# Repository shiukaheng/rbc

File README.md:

# 🤖 RoboCapture
A photogrammetry robot designed from scratch to autonomously scan indoor spaces.

## 🛠 Development

- **Cross-Platform**: This repository is designed to be cross-platform, working on Windows, MacOS, and Linux. We leverage Docker and the devcontainer extension in VSCode to achieve this.
  
- **Testing**: Most of the development and testing have been done on Linux. However, it might require slight adjustments when setting up on other operating systems.

### 🔧 Pre-requisites

1. `$(hostname).local` should be broadcasted on the network using mDNS. This applies to both the robot and the development computer.
2. Docker must be running on a Linux environment.

### 🍎 MacOS Specifics

If you're on a Mac, you might need to adjust the Docker permissions:
```bash
sudo chown -R $(whoami) ~/.docker
```
This ensures Docker can run without requiring sudo every time.

### 🖥️ X11 Authentication

For enabling X11 forwarding, execute the following command on the host computer:
```bash
xhost +local:docker
```

### 📝 Notes
Please double-check the file permissions before making a commit to ensure they are appropriate, due to docker created files being owned by `root`. Fix shall be issued soon.

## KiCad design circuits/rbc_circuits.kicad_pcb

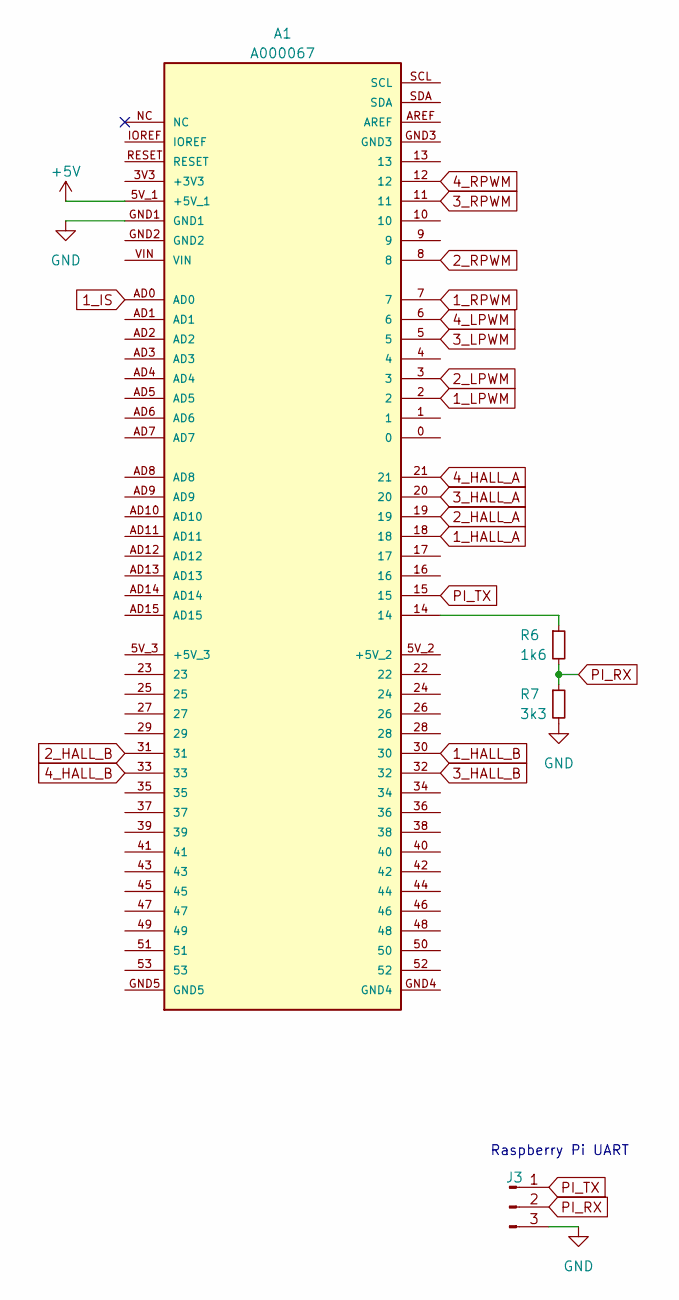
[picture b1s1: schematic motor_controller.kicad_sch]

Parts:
A1: A000067; ARDUINO_A000067
J3: Conn_01x03_Pin
R6: 1k6
R7: 3k3

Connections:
1_HALL_A: A1.18; also elsewhere on the board
1_HALL_B: A1.30; also elsewhere on the board
1_LPWM: A1.2; also elsewhere on the board
1_RPWM: A1.7; also elsewhere on the board
2_HALL_A: A1.19; also elsewhere on the board
2_HALL_B: A1.31; also elsewhere on the board
2_IS: A1.AD1; also elsewhere on the board
2_LPWM: A1.3; also elsewhere on the board
2_RPWM: A1.8; also elsewhere on the board
3_HALL_A: A1.20; also elsewhere on the board
3_HALL_B: A1.32; also elsewhere on the board
3_IS: A1.AD2; also elsewhere on the board
3_LPWM: A1.5; also elsewhere on the board
3_RPWM: A1.11; also elsewhere on the board
4_HALL_A: A1.21; also elsewhere on the board
4_HALL_B: A1.33; also elsewhere on the board
4_IS: A1.AD3; also elsewhere on the board
4_LPWM: A1.6; also elsewhere on the board
4_RPWM: A1.12; also elsewhere on the board
+5V: A1.5V_1 (+5V_1); also elsewhere on the board
PI_TX: A1.15, J3.1

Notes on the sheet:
Raspberry Pi UART

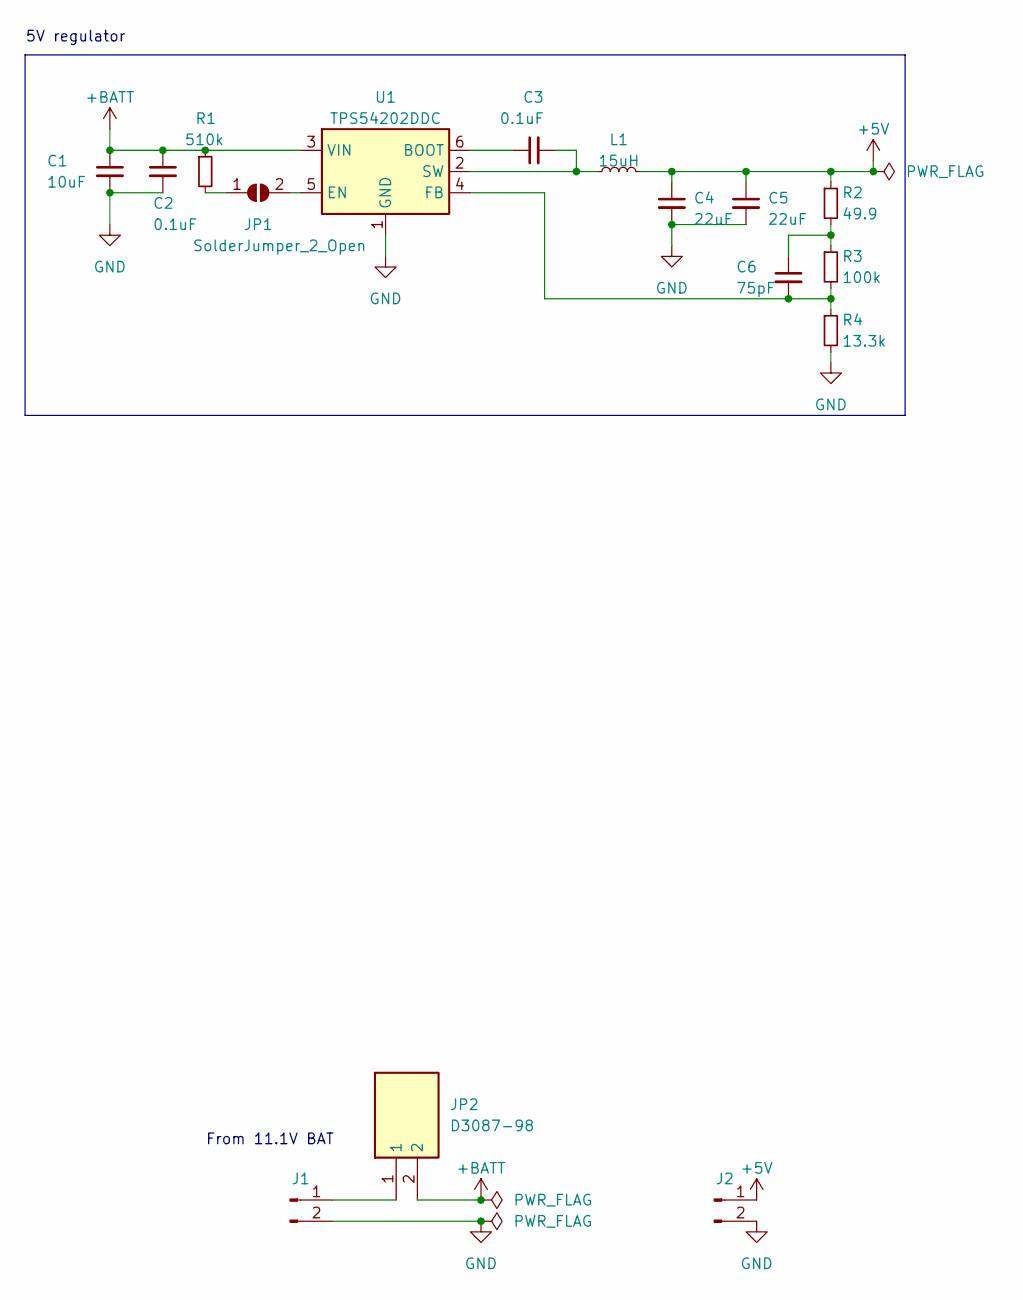
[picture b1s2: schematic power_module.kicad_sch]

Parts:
C1: 10uF; C_1206_3216Metric_Pad1.33x1.80mm_HandSolder
C2, C3: 0.1uF; C_0603_1608Metric_Pad1.08x0.95mm_HandSolder
C4, C5: 22uF; C_1206_3216Metric_Pad1.33x1.80mm_HandSolder
C6: 75pF; C_0805_2012Metric_Pad1.18x1.45mm_HandSolder
J1: Conn_01x02_Pin; TerminalBlock_Phoenix_MKDS-3-2-5.08_1x02_P5.08mm_Horizontal
J2: Conn_01x02_Pin; PinHeader_1x02_P2.54mm_Vertical
JP1: SolderJumper_2_Open; SolderJumper-2_P1.3mm_Open_RoundedPad1.0x1.5mm
JP2: D3087-98; D308798; Mouser Part Number 855-D3087-98
L1: 15uH; IND_LQH3NPH150MMEL
R1: 510k; R_0805_2012Metric_Pad1.20x1.40mm_HandSolder
R2: 49.9; R_0805_2012Metric_Pad1.20x1.40mm_HandSolder
R3: 100k; R_1206_3216Metric_Pad1.30x1.75mm_HandSolder
R4: 13.3k; R_0805_2012Metric_Pad1.20x1.40mm_HandSolder
U1: TPS54202DDC; SOT-23-6

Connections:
+5V: C4.1, C5.1, J2.1, L1.2, R2.1; also elsewhere on the board
+BATT: C1.1, C2.1, JP2.2, R1.1, U1.3 (VIN)
unnamed: C6.1, R2.2, R3.1
unnamed: J1.1, JP2.1
unnamed: JP1.1 (A), R1.2
unnamed: JP1.2 (B), U1.5 (EN)
unnamed: C3.1, U1.6 (BOOT)
unnamed: C6.2, R3.2, R4.1, U1.4 (FB)
unnamed: C3.2, L1.1, U1.2 (SW)

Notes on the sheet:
From 11.1V BAT
5V regulator

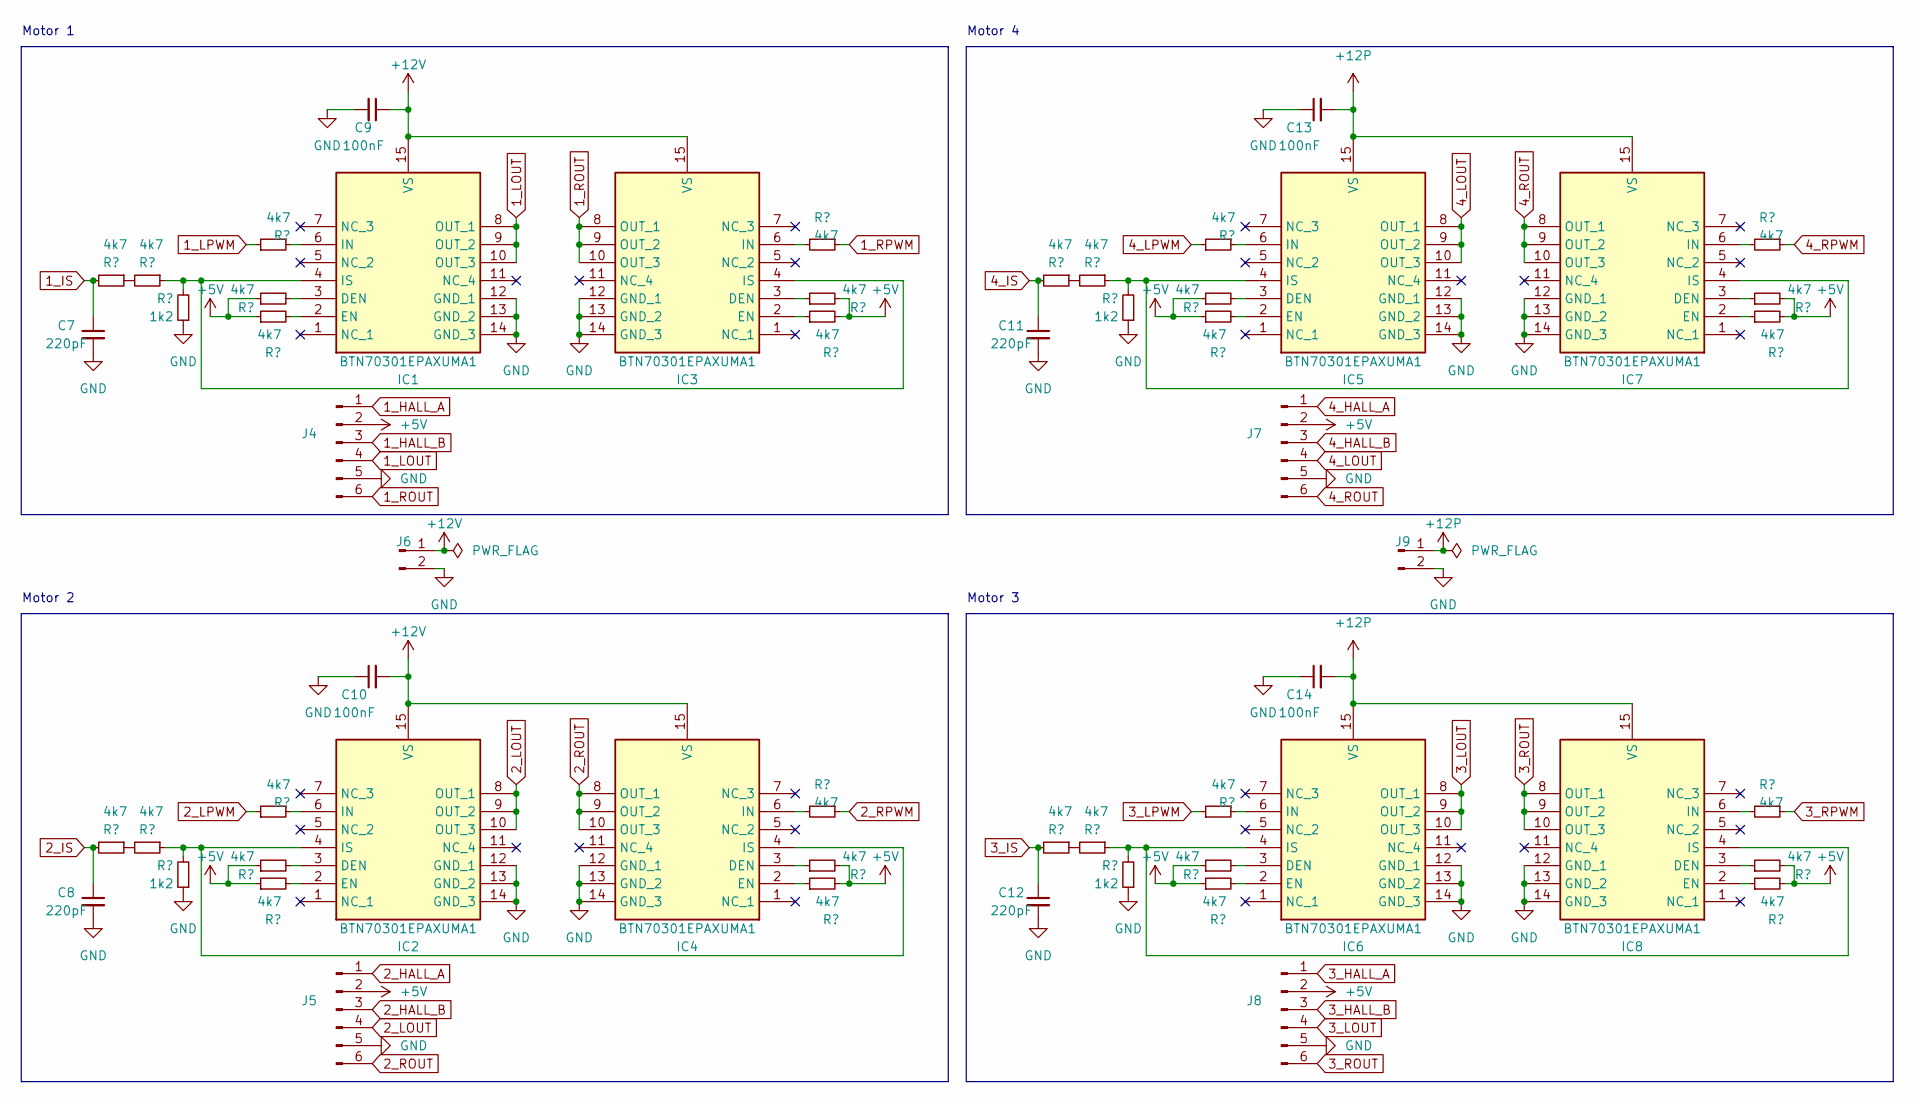
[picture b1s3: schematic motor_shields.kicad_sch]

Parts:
C7, C8, C11, C12: 220pF; C_0402_1005Metric_Pad0.74x0.62mm_HandSolder
C9, C10, C13, C14: 100nF; C_0603_1608Metric_Pad1.08x0.95mm_HandSolder
IC1, IC2, IC3, IC4, IC5, IC6, IC7, IC8: BTN70301EPAXUMA1; Infineon_PG-TSDSO-14-22_custom; Mouser Part Number 726-BTN70301EPAXUMA1
J4, J5, J7, J8: Conn_01x06_Pin; Molex_Micro-Fit_3.0_43045-0612_2x03_P3.00mm_Vertical
J6, J9: Conn_01x02_Pin; TerminalBlock_Phoenix_MKDS-3-2-5.08_1x02_P5.08mm_Horizontal
R7, R8, R9, R10, R13, R14, R15, R16, R17, R18, R19, R20, R21, R22, R23, R24, R25, R26, R27, R28, R31, R32, R33, R34, R35, R36, R37, R38, R39, R40, R41, R42: 4k7; R_1206_3216Metric_Pad1.30x1.75mm_HandSolder
R11, R12, R29, R30: 1k2; R_1206_3216Metric_Pad1.30x1.75mm_HandSolder

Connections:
1_HALL_A: J4.1; also elsewhere on the board
1_HALL_B: J4.3; also elsewhere on the board
1_LOUT: IC1.8 (OUT_1), IC1.9 (OUT_2), IC1.10 (OUT_3), J4.4
1_LPWM: R13.1; also elsewhere on the board
1_ROUT: IC3.8 (OUT_1), IC3.9 (OUT_2), IC3.10 (OUT_3), J4.6
1_RPWM: R19.1; also elsewhere on the board
2_HALL_A: J5.1; also elsewhere on the board
2_HALL_B: J5.3; also elsewhere on the board
2_IS: C8.1, R8.2; also elsewhere on the board
2_LOUT: IC2.8 (OUT_1), IC2.9 (OUT_2), IC2.10 (OUT_3), J5.4
2_LPWM: R16.1; also elsewhere on the board
2_ROUT: IC4.8 (OUT_1), IC4.9 (OUT_2), IC4.10 (OUT_3), J5.6
2_RPWM: R22.1; also elsewhere on the board
3_HALL_A: J8.1; also elsewhere on the board
3_HALL_B: J8.3; also elsewhere on the board
3_IS: C12.1, R26.2; also elsewhere on the board
3_LOUT: IC6.8 (OUT_1), IC6.9 (OUT_2), IC6.10 (OUT_3), J8.4
3_LPWM: R34.1; also elsewhere on the board
3_ROUT: IC8.8 (OUT_1), IC8.9 (OUT_2), IC8.10 (OUT_3), J8.6
3_RPWM: R40.1; also elsewhere on the board
4_HALL_A: J7.1; also elsewhere on the board
4_HALL_B: J7.3; also elsewhere on the board
4_IS: C11.1, R25.2; also elsewhere on the board
4_LOUT: IC5.8 (OUT_1), IC5.9 (OUT_2), IC5.10 (OUT_3), J7.4
4_LPWM: R31.1; also elsewhere on the board
4_ROUT: IC7.8 (OUT_1), IC7.9 (OUT_2), IC7.10 (OUT_3), J7.6
4_RPWM: R37.1; also elsewhere on the board
+5V: J4.2, J5.2, J7.2, J8.2, R14.1, R15.1, R17.1, R18.1, R20.2, R21.2, R23.2, R24.2, R32.1, R33.1, R35.1, R36.1, R38.2, R39.2, R41.2, R42.2; also elsewhere on the board
+12P: C13.2, C14.2, IC5.15 (VS), IC6.15 (VS), IC7.15 (VS), IC8.15 (VS), J9.1
+12V: C9.1, C10.2, IC1.15 (VS), IC2.15 (VS), IC3.15 (VS), IC4.15 (VS), J6.1
unnamed: IC1.3 (DEN), R14.2
unnamed: IC1.2 (EN), R15.2
unnamed: IC1.6 (IN), R13.2
unnamed: IC1.4 (IS), IC3.4 (IS), R9.1, R11.2
unnamed: IC2.3 (DEN), R17.2
unnamed: IC2.2 (EN), R18.2
unnamed: IC2.6 (IN), R16.2
unnamed: IC2.4 (IS), IC4.4 (IS), R10.1, R12.2
unnamed: IC3.3 (DEN), R20.1
unnamed: IC3.2 (EN), R21.1
unnamed: IC3.6 (IN), R19.2
unnamed: IC4.3 (DEN), R23.1
unnamed: IC4.2 (EN), R24.1
unnamed: IC4.6 (IN), R22.2
unnamed: IC5.3 (DEN), R32.2
unnamed: IC5.2 (EN), R33.2
unnamed: IC5.6 (IN), R31.2
unnamed: IC5.4 (IS), IC7.4 (IS), R27.1, R29.2
unnamed: IC6.3 (DEN), R35.2
unnamed: IC6.2 (EN), R36.2
unnamed: IC6.6 (IN), R34.2
unnamed: IC6.4 (IS), IC8.4 (IS), R28.1, R30.2
unnamed: IC7.3 (DEN), R38.1
unnamed: IC7.2 (EN), R39.1
unnamed: IC7.6 (IN), R37.2
unnamed: IC8.3 (DEN), R41.1
unnamed: IC8.2 (EN), R42.1
unnamed: IC8.6 (IN), R40.2
unnamed: R8.1, R10.2
unnamed: R25.1, R27.2
unnamed: R26.1, R28.2

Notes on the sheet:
Motor 2
Motor 3
Motor 4
Motor 1

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
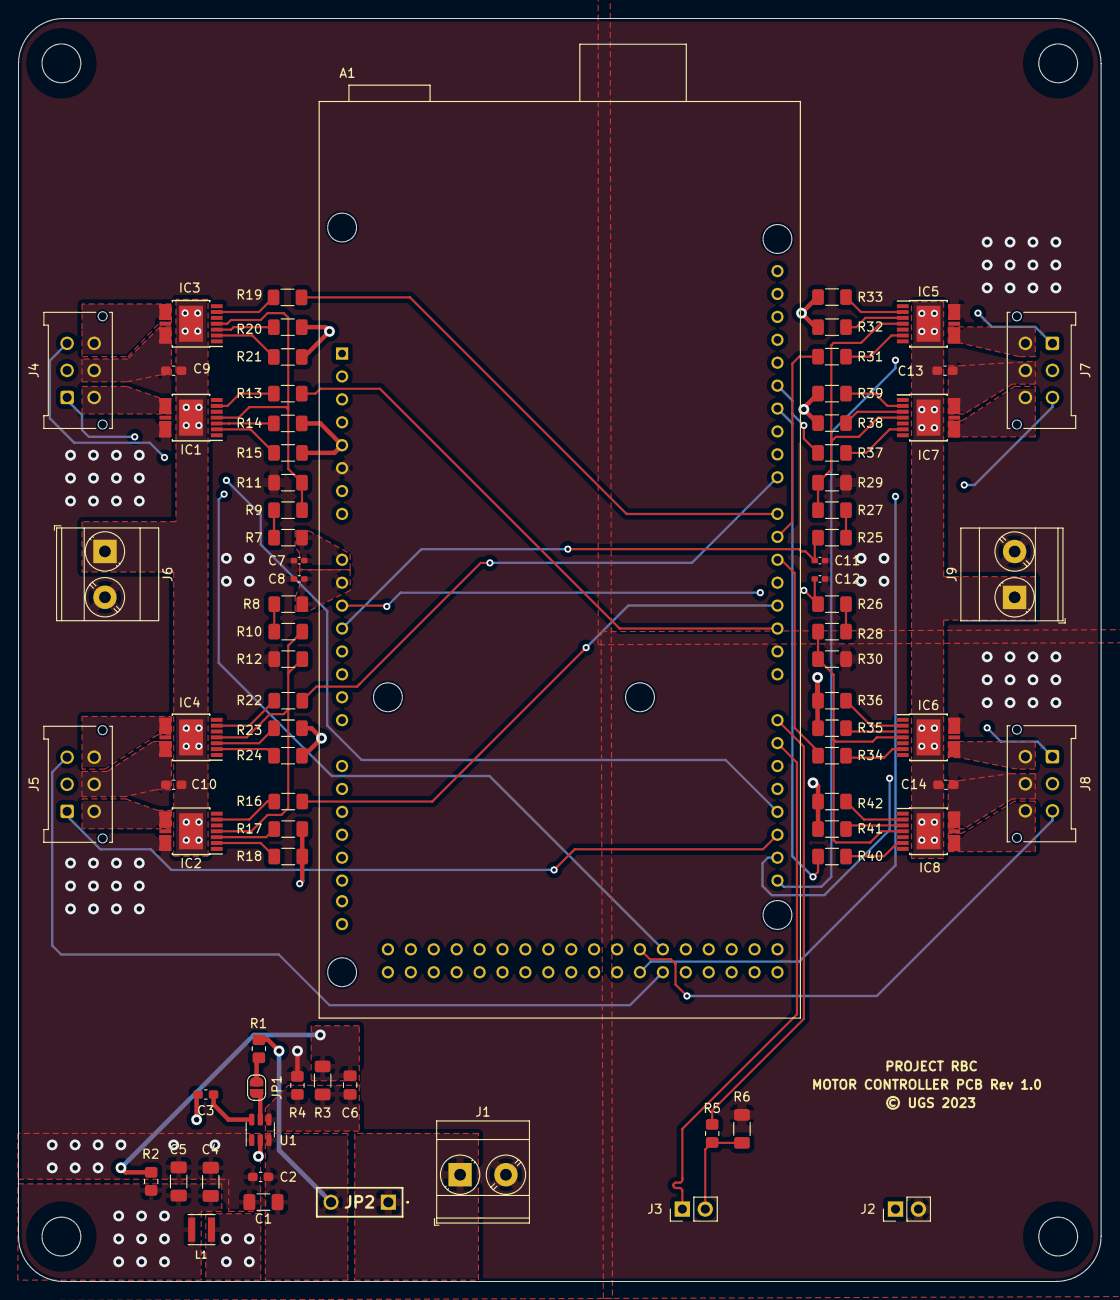
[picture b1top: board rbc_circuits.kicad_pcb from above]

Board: 4 copper layers, 120.0 x 140.0 mm, 78 parts (0 on the bottom side), 75 nets.

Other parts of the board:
R5: 1k6; R_0805_2012Metric_Pad1.20x1.40mm_HandSolder

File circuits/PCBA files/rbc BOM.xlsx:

Comment | Designator | Footprint | JLCPCB Part #
DNP | A1 | A000067:ARDUINO_A000067
10uF | C1 | Capacitor_SMD:C_1206_3216Metric_Pad1.33x1.80mm_HandSolder | C396795
0.1uF | C2, C3 | Capacitor_SMD:C_0603_1608Metric_Pad1.08x0.95mm_HandSolder
22uF | C4, C5 | Capacitor_SMD:C_1206_3216Metric_Pad1.33x1.80mm_HandSolder | C909845
75pF | C6 | Capacitor_SMD:C_0805_2012Metric_Pad1.18x1.45mm_HandSolder
220pF | C7, C8, C11, C12 | Capacitor_SMD:C_0402_1005Metric_Pad0.74x0.62mm_HandSolder | C513697
100nF | C9, C10, C13, C14 | Capacitor_SMD:C_0603_1608Metric_Pad1.08x0.95mm_HandSolder | C307348
BTN70301EPAXUMA1 | IC1, IC2, IC3, IC4, IC5, IC6, IC7, IC8 | Infineon_PG-TSDSO-14-22 | C3655686
Conn_01x02_Pin | J1, J6, J9 | TerminalBlock_Phoenix:TerminalBlock_Phoenix_MKDS-3-2-5.08_1x02_P5.08mm_Horizont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 | C89120
DNP | J2, J3 | Connector_PinHeader_2.54mm:PinHeader_1x02_P2.54mm_Vertical
Conn_01x06_Pin | J4, J5, J7, J8 | Connector_Molex:Molex_Micro-Fit_3.0_43045-0612_2x03_P3.00mm_Vertical | C234188
DNP | JP1 | Jumper:SolderJumper-2_P1.3mm_Open_RoundedPad1.0x1.5mm
DNP | JP2 | D308798
15uH | L1 | LQH3NPH150MMEL:IND_LQH3NPH150MMEL | C668450
510k | R1 | Resistor_SMD:R_0805_2012Metric_Pad1.20x1.40mm_HandSolder | C316820
49.9 | R2 | Resistor_SMD:R_0805_2012Metric_Pad1.20x1.40mm_HandSolder | C164002
100k | R3 | Resistor_SMD:R_1206_3216Metric_Pad1.30x1.75mm_HandSolder | C881326
13.3k | R4 | Resistor_SMD:R_0805_2012Metric_Pad1.20x1.40mm_HandSolder | C170785
1.6k | R5 | Resistor_SMD:R_0805_2012Metric_Pad1.20x1.40mm_HandSolder | C316776
3.3k | R6 | Resistor_SMD:R_1206_3216Metric_Pad1.30x1.75mm_HandSolder | C104771
4.7k | R7, R8, R9, R10, R13, R14, R15, R16, R17, R18, R19, R20, R21, R22, R23, R24, R2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 | Resistor_SMD:R_1206_3216Metric_Pad1.30x1.75mm_HandSolder | C432834
1.2k | R11, R12, R29, R30 | Resistor_SMD:R_1206_3216Metric_Pad1.30x1.75mm_HandSolder | C340507
TPS54202DDC | U1 | Package_TO_SOT_SMD:SOT-23-6 | C191884

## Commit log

2023-01-05 vscode stuff
2023-01-05 formatting
2023-05-14 restructure
2023-05-16 restructuring
2023-05-27 migration
2023-05-29 added controller
2023-05-29 rename
2023-05-29 more renaming
2023-05-29 added READMEs
2023-05-29 functional devcontainer
2023-05-29 Added instructions of MacOS devcontainer workflow
2023-05-30 improved dev container
2023-05-30 added more devcontainer dependencies
2023-05-30 permissions fix
2023-05-30 forwarding usb
2023-05-30 convenience functions
2023-05-30 fixed some include issues and library install
2023-05-30 started work on ROSSerialClient
2023-05-30 fixed more includes!
2023-05-31 first draft of controller
2023-05-31 added pid parameter controls
2023-05-31 removed potentially problematic consts
2023-05-31 control node functional but unstable
2023-05-31 debug view
2023-05-31 removed ROS user
2023-05-31 automated workspace setup
2023-05-31 attempted fix
2023-05-31 NOT WORKING
2023-06-01 improved dev experience
2023-06-01 functional PID motor control!
2023-06-01 cleanup
2023-06-01 added controL_parameter_server
2023-06-02 hardware interface
2023-06-02 native RPM to rad/s conversion
2023-06-02 migrated to rad/s
2023-06-02 fixed parameter server
2023-06-02 added positional info
2023-06-02 added position to interface
2023-06-02 added effort
2023-06-02 removed talker and listener example
2023-06-02 non-functional ros_control controller
2023-06-03 controller runs (but not fully implemented)
2023-06-03 hardware interface fix
2023-06-03 cleanup controller
2023-06-04 compiles but broken
2023-06-04 semi-working controller, but wrong configuration
2023-06-04 fixed configuration
2023-06-05 rename file
2023-06-06 added copilot
2023-06-06 added odometry calculation
2023-06-06 comments, cleanup
2023-06-06 added odometry publishing
2023-06-06 wrong calculations
2023-06-06 marked potential error
2023-06-08 reconfigured to supposedly correct parameters
2023-06-08 updated controller
2023-06-10 started new implementation of kinematics
2023-06-10 inverse kinematics, and composition
2023-06-10 added odometry to new .h file
2023-06-10 fixed kinematics
2023-06-10 fixed odometry numerical stability issue
2023-06-10 remove debug message
2023-06-10 fixed wrong commenting
2023-06-10 changed to dumber encoder
2023-06-10 migrated files in
2023-06-12 fixed wheel direction and names
2023-06-13 added model view
2023-06-13 fixed names
2023-06-13 changed to using joint state controller
2023-06-13 broken gazebo
2023-06-13 initial commit for rbc circuits
2023-06-14 added 5V reg circuit
2023-06-14 astra
2023-06-14 added astra
2023-06-15 orbbec
2023-06-15 fix dockerfile
2023-06-15 Update Dockerfile
2023-06-15 motor shield circuit
    BTN7030-1EPA
2023-06-15 added more support for running on rpi
2023-06-15 added orbbec_astra code
2023-06-15 updated paths
2023-06-15 convenience function things
2023-06-15 added remote launch file
2023-06-15 more remote bot stuff
2023-06-15 added joint state controller
2023-06-15 fixed network config
2023-06-15 added laser
2023-06-15 slam stuff
2023-06-16 updated shield schematic
2023-06-16 added dependencies
2023-06-17 added emergency stop and resume methods to controller class
2023-06-17 started work on services
2023-06-18 diagram and cleanup
2023-06-19 testing
2023-06-22 cleanup unused classes
2023-06-22 updated orbbec packages
2023-06-22 updated controlled code
2023-06-22 improved PID algorithm
    added mirrored bias to PID
    modified integer term to switch polarity depending on setpoint polarity
    disabled stalling prevention
2023-06-22 changed stall prevention
2023-06-22 added derivative constrainer (unused for now)
2023-06-22 added quantization error as deadband
2023-06-22 fixed bugs with quantization error calc
2023-06-23 removed unused service files
2023-06-23 started control benchmarking tools
2023-06-23 modified i term
2023-06-23 good control
2023-06-23 started work on PID rewrite
2023-06-24 change initial parameter passing
2023-06-24 controller overhaul
2023-06-24 work on rewrite
2023-06-24 general flow set up
2023-06-24 encoder implementation
2023-06-25 pid implemented?
2023-06-25 fixed pid
2023-06-25 motor done
2023-06-25 start work on communication
2023-06-25 demoted old controller source and probably functionally communication
2023-06-25 updated messages
2023-06-25 new controller code compiles
2023-06-25 comments
2023-06-25 removed deadband
2023-06-25 debugging why params not received
2023-06-25 experiment with free spinning controller
2023-06-25 removed distraction
2023-06-25 removed distractions, and multiple control implementations
2023-06-25 python testing
2023-06-26 a seemlingly good tuning
2023-06-27 more convenience functions!
2023-06-27 clean up controller and init scripts
2023-06-27 fix orbbec_astra, move to lib
2023-07-09 state manager outline
2023-07-09 some more research
2023-07-10 proposed split
2023-07-10 untested
2023-07-10 renaming
2023-07-10 quote fix
2023-07-11 better launchfile management node
2023-07-13 fixed perms
2023-07-13 minimize docker launch requirements
2023-07-13 fixed gitignore
2023-07-13 fixed missing package.xml
2023-07-13 more work on monitored launchfile
2023-07-25 controller pcb rev 1
2023-07-31 more rbc_state_manager stuff
2023-07-31 web interface package
2023-08-13 omniwheel base custom controller; changed PWM freq to accommodate new ICs
2023-08-13 LED movement signal; ssh uncomment
2023-08-14 Arduino GPIO UART update
2023-08-14 updated ArdunioHardware.h to
2023-08-16 Created rbc_capture package and hello_publisher.py
2023-08-20 added current sense pins
2023-08-22 even more convienent
2023-08-22 fixed and improved dx
2023-08-22 renamed / hid web package for now
2023-08-22 yikers
2023-08-22 added timerinterrupt for current sense
2023-08-22 more convenience stuff
2023-08-22 current sense now process all 4 motors
2023-08-22 onboard led fixed
2023-08-22 included icurrent in communication.h
2023-08-22 bug fixed icurrent
2023-08-22 rbcinfo
2023-08-22 more dx
2023-08-22 syncbot
2023-08-22 added bot scripts
2023-08-22 factored out variables
2023-08-22 outline of lidar launch
2023-08-23 fixed issues, more dx
2023-08-23 refactor packages
2023-08-23 fix cb
2023-08-23 new packages
2023-08-23 fixed ac
2023-08-23 dumb fixes
2023-08-23 fix abl
2023-08-23 MARK OF THIS REPO WORKING OK
2023-08-23 COMPLETELY REWRITTEN BASHY BASHY STUFF
2023-08-23 minor fix for bot compatibility
2023-08-23 current sense up and running
2023-08-23 fixed service
2023-08-23 fixed links
2023-08-23 fixed building libs
2023-08-23 auto setbotmaster
2023-08-23 Noice
2023-08-23 it just works?
2023-08-23 shortcuts
2023-08-23 log & dev
2023-08-23 update lidar position
2023-08-25 params set
2023-08-25 fixed wheel configuration
2023-08-29 fixed lost sync
    baud rate doubled
2023-08-29 fixed rviz rbc orientation
2023-08-31 SLAM first commit
2023-09-06 fixed controller parameters
2023-09-06 removed non-essential topics for stability
2023-09-06 fixed odometry
2023-09-07 functional move_base launch file
2023-09-07 added acceleration bounding to controller
2023-09-07 better visualization
2023-09-07 corrected parameters
2023-09-07 lowered acceleration limit
2023-09-07 exploration
2023-09-09 PCB Rev2.0 publish
    It's here
2023-09-11 initial commit
    This branch changes odom to a 3 wheel configuration
2023-09-11 updated wheel coordinates&angles
2023-09-12 wltf
2023-09-12 disabled slam for debugging
2023-09-13 removed .old
2023-09-13 updated wheel position
    wheel-origin distance: 0.45m -> 0.2m
2023-09-13 updated mesh for chassis 2.0
2023-09-13 removed unused mesh files
2023-09-13 updated wheel 1 coordinates
2023-09-13 updated wheels xacro
2023-09-13 enabled slam
2023-09-14 Finish "request_camera_info" service and "CameraInfo" message type
2023-09-15 mesh successfully loaded
2023-09-15 updated lidar location and orientation
2023-09-15 removed redundant mesh
2023-09-15 updated chassis inertial and collision model
2023-09-15 removed redundant lines
2023-09-16 Finished camera capture function
    Note that file path has not been defined.
2023-09-16 enable motor ICs at the start
2023-09-16 battery monitor setup
    To-do:
    implement LED indicators for battery level.
    Append battery level to ROS message
    Define robot behaviour when low voltage
2023-09-17 battery LEDs should light up according to level
2023-09-17 added low battery and emergency stop behaviour
    These conditions are only triggered when 6S battery is connected and solder jumper is in place
2023-09-30 clean slate
2023-10-06 added meta files
2023-12-24 initial commit
    included battery level detection library
2023-12-24 added battery detection code
2023-12-24 trying new board
2023-12-24 battery display
2023-12-26 power management logic and reset pin
2023-12-26 modify for 3 motors
2023-12-26 fixed bugs
2023-12-28 changed messages to 3 wheels

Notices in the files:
circuits/rbc_circuits.kicad_pcb:
© UGS 2023
